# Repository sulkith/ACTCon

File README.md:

# ACTCon
Buttonbox and additional Force Feedback with a Teensy Controller for Assetto Corsa

Currently the Arduino Pro Micro is used. This Chip is much cheaper and sufficient for the Task.
The current State is a Board with an Arduino Pro Micro and two LED Circles with RGB Leds as Dials.
There is an aditional RGB-LED Strip for shift indicator.
Additionaly there is a 1.8' Display which shows informations about:
  - Velocity
  - Engine Speed
  - Current Gear
  - Traction Control
  - Anti Blocking System
  - current lap Time
  - best lap Time

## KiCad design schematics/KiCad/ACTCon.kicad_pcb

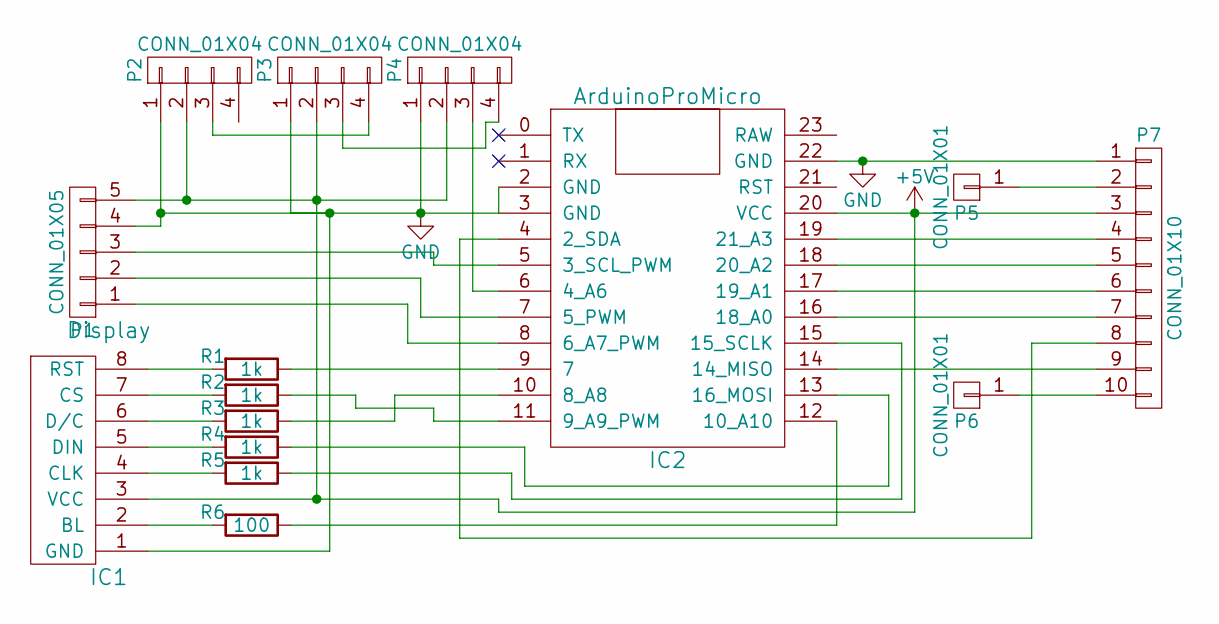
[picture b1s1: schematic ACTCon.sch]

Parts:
IC1: Display; Pin_Header_Straight_1x08
IC2: ArduinoProMicro
P1: CONN_01X05; Pin_Header_Straight_1x05
P2, P3, P4: CONN_01X04; Pin_Header_Straight_1x04
P5, P6: CONN_01X01; Pin_Header_Straight_1x01
P7: CONN_01X10; Pin_Header_Straight_1x10
R1, R2, R3, R4, R5: 1k; R_0603_HandSoldering
R6: 100; R_0603_HandSoldering

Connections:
+5V: IC1.3 (VCC), IC2.20 (VCC), P1.5, P2.2, P3.2, P4.2, P7.3
GND: IC1.1 (GND), IC2.2 (GND), IC2.3 (GND), IC2.22 (GND), P1.4, P2.1, P3.1, P4.1, P7.1
unnamed: IC1.2 (BL), R6.2
unnamed: IC1.4 (CLK), R5.2
unnamed: IC1.5 (DIN), R4.2
unnamed: IC1.6 (D/C), R3.2
unnamed: IC1.7 (CS), R2.2
unnamed: IC1.8 (RST), R1.2
unnamed: IC2.4 (2_SDA), P7.8
unnamed: IC2.5 (3_SCL_PWM), P1.3
unnamed: IC2.6 (4_A6), P4.3
unnamed: IC2.7 (5_PWM), P1.2
unnamed: IC2.8 (6_A7_PWM), P1.1
unnamed: IC2.9 (7), R1.1
unnamed: IC2.10 (8_A8), R3.1
unnamed: IC2.11 (9_A9_PWM), R2.1
unnamed: IC2.12 (10_A10), R6.1
unnamed: IC2.13 (16_MOSI), R4.1
unnamed: IC2.14 (14_MISO), P7.9
unnamed: IC2.15 (15_SCLK), R5.1
unnamed: IC2.16 (18_A0), P7.7
unnamed: IC2.17 (19_A1), P7.6
unnamed: IC2.18 (20_A2), P7.5
unnamed: IC2.19 (21_A3), P7.4
unnamed: P2.3, P3.4
unnamed: P3.3, P4.4
unnamed: P5.1, P7.2
unnamed: P6.1, P7.10

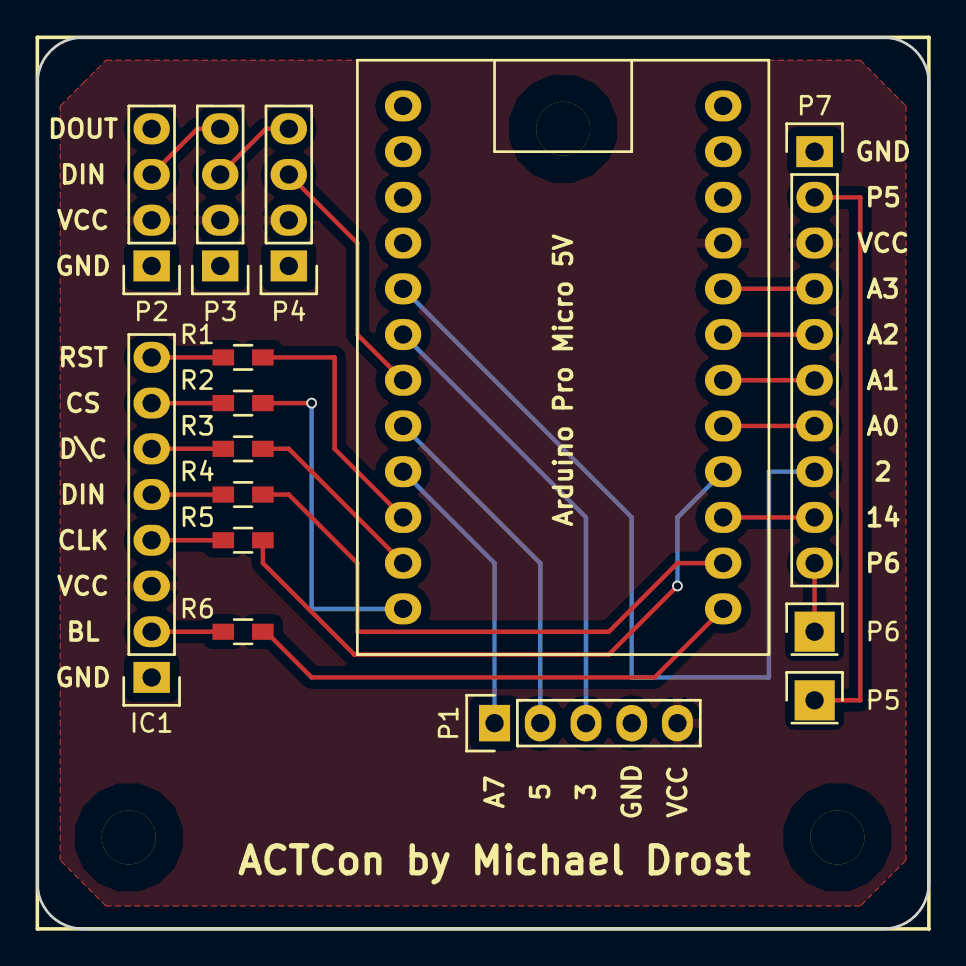
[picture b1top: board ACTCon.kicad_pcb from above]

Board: 2 copper layers, 49.5 x 49.5 mm, 15 parts (0 on the bottom side), 28 nets.

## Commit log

2015-12-20 Initial Import
2015-12-20 Added Schematic
2015-12-20 Added Sample For Button Press forwarding with Bounce Class. Works in Assetto Corsa for Traction Control
    schematics/Version2_WithButton.fzz can be used for this sample. But disable the Vibration motor first since it is not disabled by the sketch
2016-01-16 Improved Stability of the Program and the network connection. Also optimized it for slower Controllers
2016-01-16 Added a WS2812 LED Strip for the RPM. Softwar is also compatible with a Sparkfun Pro Micro now. The Sparkfun chip is only working with the new Host Application from the last commit.
2016-01-18 Added Project Structure for the Teensy Program. Reinvented the Serial Communication. Added Configuration File.
    Needed some Changes on the PC SW to get the Communication working.
2016-01-24 Modified Receiving. It spawns a new Thread now. This reduces the latency significantly!. Needs Cleanup ;-)
2016-01-24 Added A ST7753 Display
2016-01-24 Working on Pro Micro. Not on the Teensy -.-
2016-01-24 Added Current and last Lap Time
2016-02-07 Increased led Brightness
2016-02-07 Filter for maxrpm. Maxrpm is now only measured in N
2016-02-07 Restructured an refactored the code For the WS2812 LEDs. Now it is possible to use an LED in different Colors for different applications.
2016-02-07 Added license Header to all Files
2016-02-07 Added G-Force Display.
2016-02-21 Separated component Specific Configurations
2016-02-21 Added the ability of using inputs as keyboard presses. Added a reini section to reinitialize the system. e.g. maxrpm etc. some Cleanup: removed the old led blinking pin for maxrpm.
2016-02-21 Added Pin to reset the saved Values and tested it. PIN6 now has to be pulled to VCC to keep the controller from resetting unintentionally.
2016-02-21 Optimized input process of the Digital Input Process
2016-02-21 Formatting
2016-02-22 Fixed a critical Bug in the action Scheduler
2016-02-22 restructured KeyboardOutput to be recognized by AssettoCorsa
2016-05-27 Added Startup Test
2016-05-27 some reconfigurations for the soldered Board
2016-05-28 Fixed Pullup Functionality in the digital Input Function
2016-05-28 Adapted to new Board. added second Dial.
2016-05-28 Added License
2016-06-05 Added Buttonbox
2016-06-05 Added T15Simulation via a Key-Switch :-)
2016-06-05 Decreased Debouncing
2016-06-05 Fixed maxrpm after startup test
2016-06-21 Added Telemetry File which is written to C:\temp
2016-07-05 Updated FileWriter for MultiEcuScan Graph output
2016-07-05 Fixed a Bug in startupTest.h Endless loop while switching on off while on hold
2016-07-07 Added schematics with KiCad. on a 5cmX5cm PCB which should be possible to produce with dirtypcbs on the cheap :-)
2016-07-11 Updated schematics. Added Drill gerber and corrected the padsize for the arduino.
2016-07-12 moved the wires around the connectors.
2016-07-15 Moved PCB description
2016-12-30 decreased led brightness
2016-12-30 some design changes
